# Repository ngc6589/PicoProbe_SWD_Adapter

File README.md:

# Raspberry Pi Pico SWD Debugger

# この基板について

PicoProbe という SWD デバッガにハーフピッチの 2x5 10pin ヘッダをつけた基板です。
SWDIO と SWCLK の 2線でデバッグするデバッガとなります。 opnocd -f interface/cmsis-dap.cfg で使用可能なデバッガですので汎用タイプになります。
ただし、<font color="red"><b>ターゲットの電圧は 3.3V 固定</b></font> となります。

基本的には 下記リンクにある NXP社の MCU-Link, MCU-Link Pro をお勧めします。数年前まで秋月などで安く購入出来た NXP LPC-Link2 の後継です。これでしたら、ターゲットの電圧 1.2V - 5V 対応です。

 [MCU-Link Debug Probe](https://www.nxp.jp/design/software/development-software/mcuxpresso-software-and-tools-/mcu-link-debug-probe:MCU-LINK)

[MCU-Link Pro Debug Probe](https://www.nxp.jp/design/software/development-software/mcuxpresso-software-and-tools-/mcu-link-pro-debug-probe:MCU-LINK-PRO)

当基板は、基本的には SWD デバッガの相性問題などで別のデバッガを試してみたいなどにご利用ください。

<b>ターゲットプロセッサやホスト OS、openocd のバージョンや openocd のコンフィグファイルなどの設定内容によって相性問題はかなりの確率で発生すると思われます。相性問題に伴う保証はできません。</b> MCU-Link もお勧めはしていますが、これも全ての環境で完璧に動くわけでも無いため同様に保証することはできません。

# 使用法

## 準備
基基板に USB ケーブルを接続し PC に接続してください。

■Windows 

CMSIS-DAP インタフェースが libusb-win32 に、シリアルポートがポート(COMとLPT)に表示されたら問題ありません。

ただし、Getting Start マニュアルには以前は libusb-win32 が必要だったけど、今はいい。とあるので、WinUSB で認識されていても問題ないと重います。最新 PicoProbe のファームウエア picoprobe-cmsis-v1.0.3 は libusb-win32 でも動いています。

現状 CMSIS-DAP が見えていたら動くと思われます。動かない場合は zadig コマンドをネットからダウンロードして、CMSIS-DAP のドライバを切り替えばいいです。

■Linux の場合は、openocd にある udev の .rules ファイルを /etc/udev/rules.d にコピーして
```
$ sudo udevadm control --reload-rules
$ sudo udevadm trigger
```

あとは、シリアルポートをユーザーが使えるように dialout グループにユーザー追加します。
```
$ sudo usermod -aG dialout ユーザー名
```

デバッグプローブを USB に挿して、/var/log/syslog に probe の CMSIS-DAP 名や、シリアルポートが ttyUSB0 などにアタッチされたメッセージがでていれば問題ありません。

# 結線

PicoProbe 基板とターゲットの基板をフラットケーブルで接続します。uart を使用する場合は、Lアングルのピンヘッダにマイコンの TX/RX を接続してください。

# vscode 表示例

「実行」「デバッグの開始」を選択してデバッグを開始します。openocd・gdb-multiarch が問題なく起動できれば、プログラムがターゲットに書き込まれてデバッグが始まります。
↓のスクリーンショットのように変数が表示されたりしていればデバッガは動いています。また、プログラムのプリント出力も、vscode のシリアルモニタに表示されていれば問題はありません。

# 回路図・ガーバーファイル
回路図は Schematic.pdf を参照してください。  
ガーバーファイルは KiCad/20231007 フォルダを参照してください。

# 部品表

上記組み立て例の部品表は以下のようになります。

|部品番号|部品名|数量|通販アドレス|備考|
|---|---|---|---|---|
|U1|Raspberry Pi Pico|1|https://akizukidenshi.com/catalog/g/gM-16132/||
|J1|ピンヘッダ　２×５（１０Ｐ）　表面実装用　１．２７ｍｍピッチ|1|https://akizukidenshi.com/catalog/g/gC-10904/||
|J2|ピンヘッダ　Ｌ型　１×３　（３Ｐ）|1|https://akizukidenshi.com/catalog/g/gC-15510/||
|SW1|タクトスイッチ|1|https://akizukidenshi.com/catalog/g/gP-03650/|リンクは黄色の例|
|R1-R4|10Ω 0603(1608)|4|||
||２×５（１０Ｐ）両端コネクタ付ＩＤＣリボンケーブル（フラットケーブル　ハーフピッチ）|1|https://akizukidenshi.com/catalog/g/gC-06776/|||
||プリント基板|1||||

# 引用
Raspberry Pi PICO の KiCad ライブラリは https://github.com/ncarandini/KiCad-RP-Pico を利用しています。

PicoProbe は、https://github.com/raspberrypi/picoprobe の公式ファームウエアを使用しています。

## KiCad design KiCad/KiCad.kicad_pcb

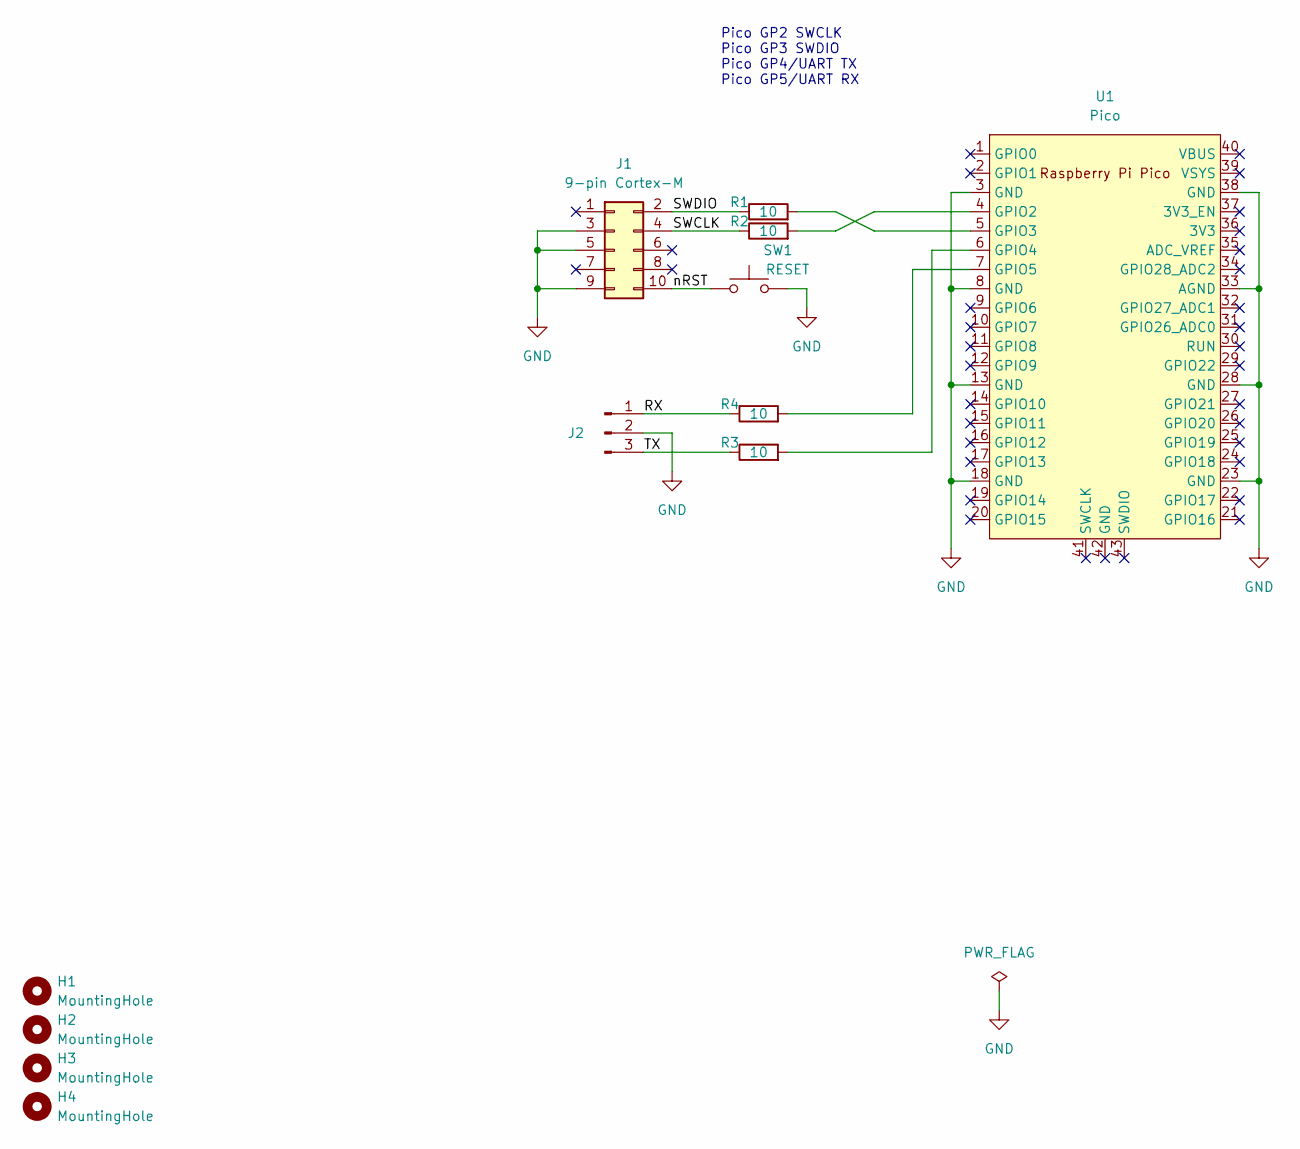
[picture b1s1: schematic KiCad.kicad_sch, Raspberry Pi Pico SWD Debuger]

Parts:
H1, H2, H3, H4: MountingHole; MountingHole_3.2mm_M3
J1: 9-pin Cortex-M; PinHeader_2x05_P1.27mm_Vertical_SMD
J2: Conn_01x03_Pin; PinHeader_1x03_P2.54mm_Horizontal
R1, R2, R3, R4: 10; R_0603_1608Metric_Pad0.98x0.95mm_HandSolder
SW1: RESET; SW_PUSH_6mm
U1: Pico; RPi_Pico_SMD_TH

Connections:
/RX: J2.1, R4.1
/SWCLK: J1.4, R2.1
/SWDIO: J1.2, R1.1
/TX: J2.3, R3.1
/nRST: J1.10, SW1.1
GND: J1.3, J1.5, J1.9, J2.2, SW1.2, U1.3 (GND), U1.8 (GND), U1.13 (GND), U1.18 (GND), U1.23 (GND), U1.28 (GND), U1.33 (AGND), U1.38 (GND)
unnamed: R2.2, U1.4 (GPIO2)
unnamed: R1.2, U1.5 (GPIO3)
unnamed: R3.2, U1.6 (GPIO4)
unnamed: R4.2, U1.7 (GPIO5)

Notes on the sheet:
Pico GP2 SWCLK Pico GP3 SWDIO Pico GP4/UART TX Pico GP5/UART RX

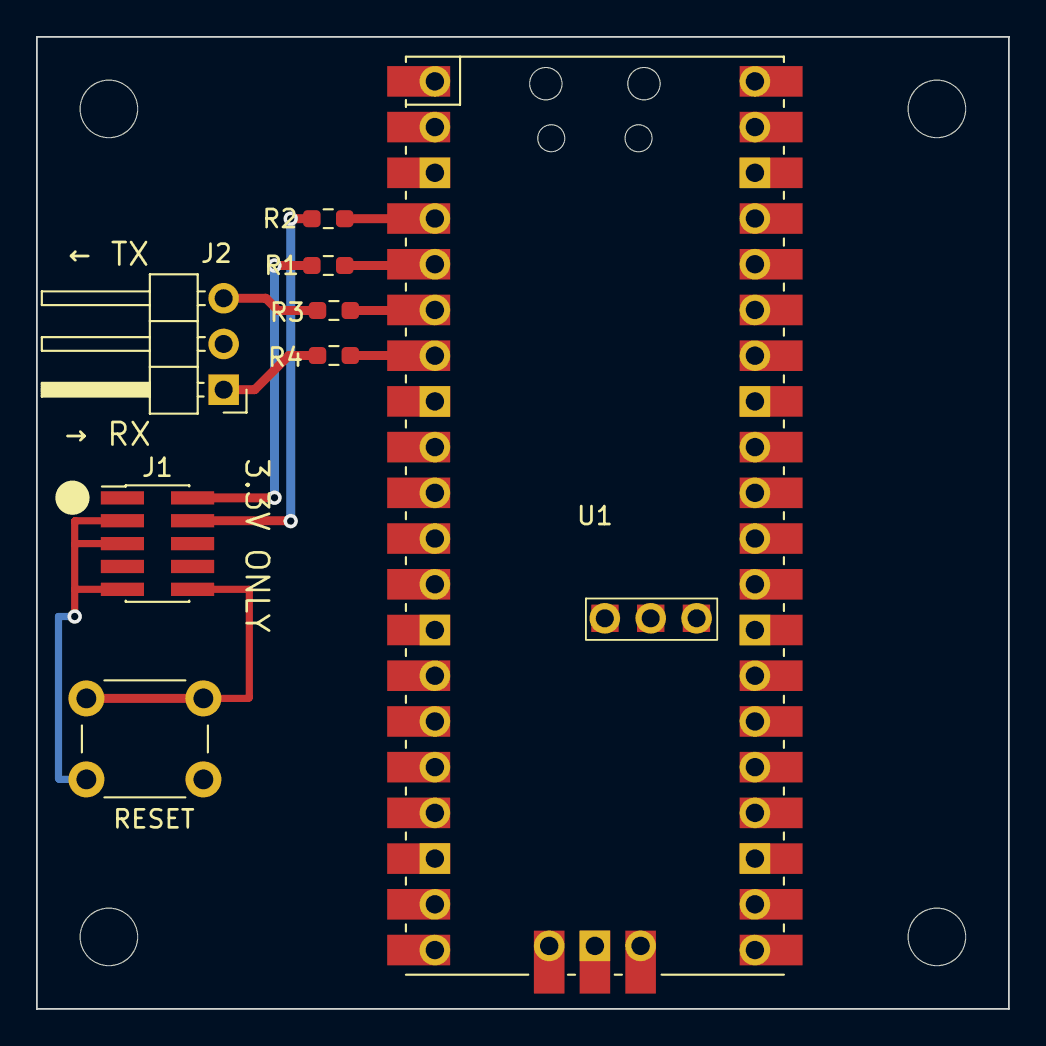
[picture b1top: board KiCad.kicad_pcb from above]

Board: 2 copper layers, 54.0 x 54.0 mm, 12 parts (0 on the bottom side), 10 nets.

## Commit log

2023-10-13 ADD NEW FILES
2023-10-13 ADD MATERIAL FOLDER
